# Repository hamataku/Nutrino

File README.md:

# Nutrino

**Nutrino** is a USB headphone amplifier featuring the application of the **Nutube**. It incorporates the PCM2704 as the codec IC and utilizes the NJM4580 for the operational amplifier in the output stage.

The circuit design was completed using Eagle. The schematic diagram is [here](misc/nutrino.pdf).

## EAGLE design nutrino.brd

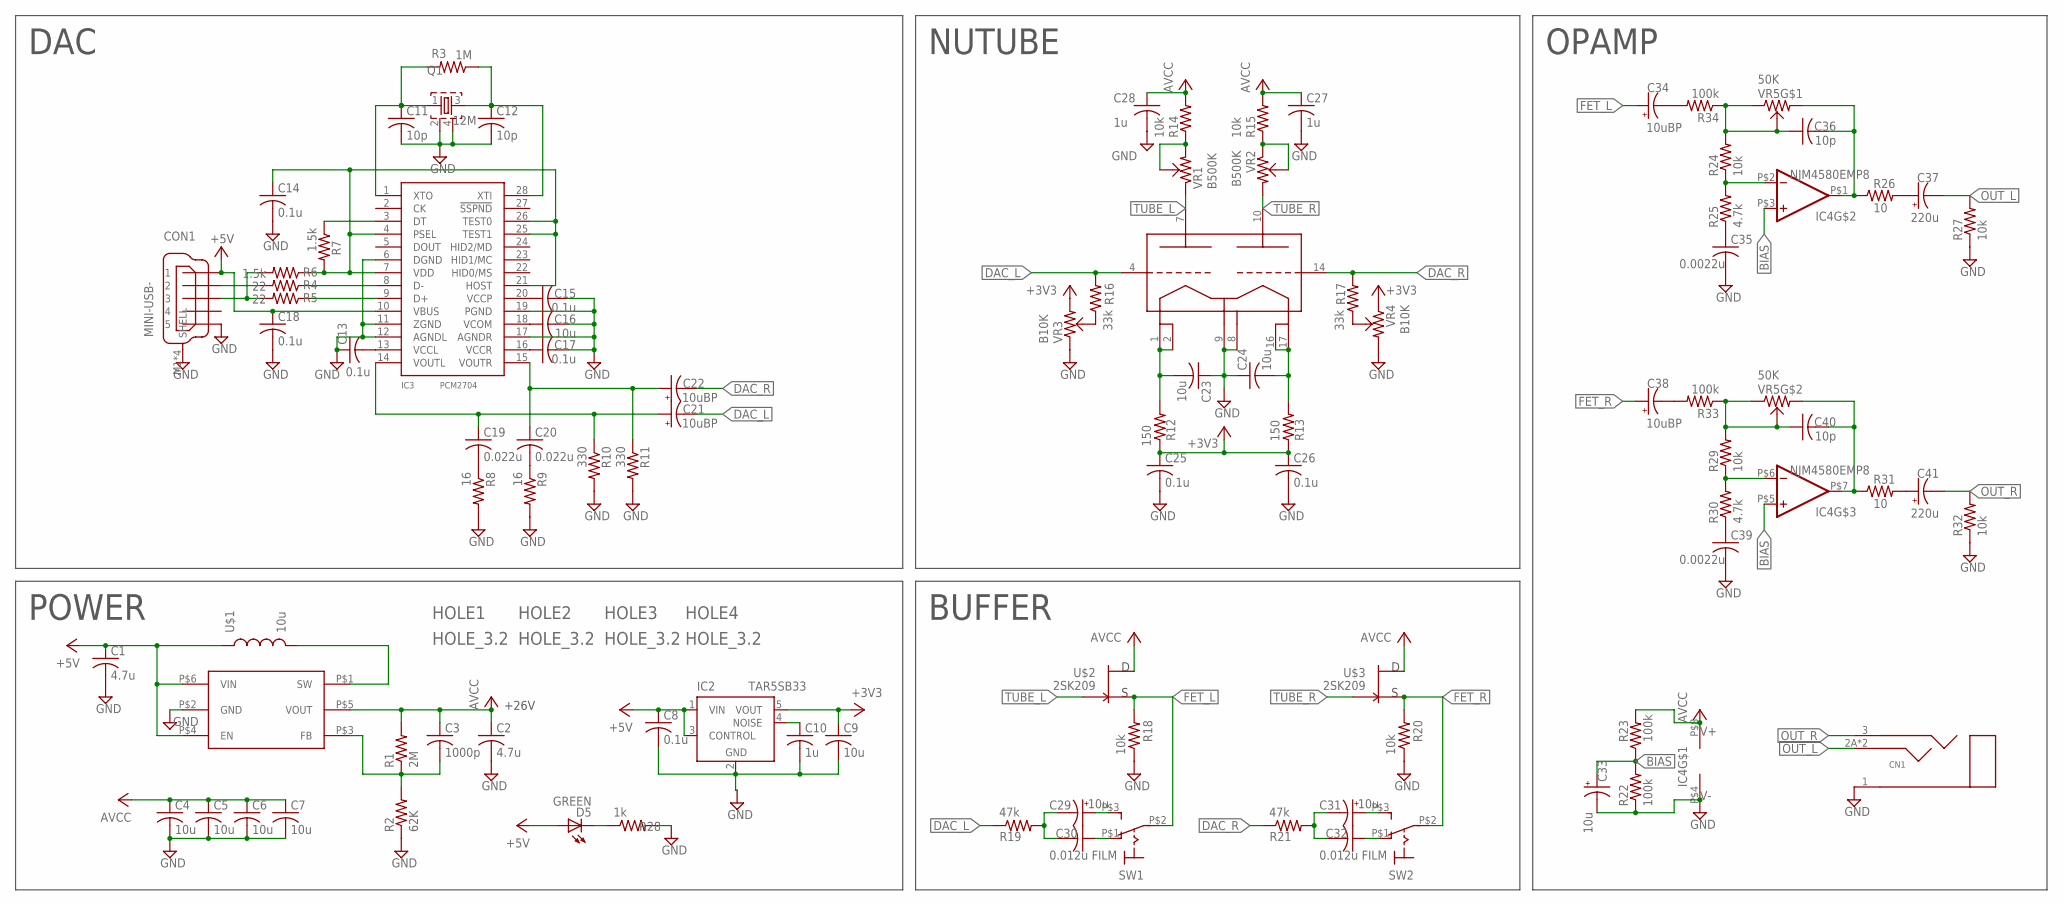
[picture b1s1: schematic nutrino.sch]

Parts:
C1, C2: 4.7u; 2012-C
C3: 1000p; 2012-C
C4, C5, C6, C7, C9: 10u; 2012-C
C8, C13, C14, C15, C17, C18, C25, C26: 0.1u; 2012-C
C10, C27, C28: 1u; 2012-C
C11, C12, C36, C40: 10p; 2012-C
C16, C23, C24: 10u; 3216
C19, C20: 0.022u; 2012-C
C21, C22, C34, C38: 10uBP; E2,5-7
C29, C31, C33: 10u; E2,5-7
C30, C32: 0.012u FILM; C050-024X044
C35, C39: 0.0022u; 2012-C
C37, C41: 220u; E2,5-7
CN1: STEREO-3.5-MJ8435; MJ8435
CON1: MINI-USB-; UX60A-MB-5ST
D5: GREEN; D2012
HOLE1, HOLE2, HOLE3, HOLE4: HOLE_3.2
IC1: TLV61046A; SOT23-6
IC2: TAR5SB33; SSOP5-P-0.95
IC3: PCM2704; SSOP28
IC4: NJM4580EMP8; EMP8
Q1: 12M; FA-238V
R1: 2M; 2012-R
R2: 62K; 2012-R
R3: 1M; 2012-R
R4, R5: 22; 2012-R
R6, R7: 1.5k; 2012-R
R8, R9: 16; 2012-R
R10, R11: 330; 2012-R
R12, R13: 150; 2012-R
R14, R15, R18, R20, R24, R27, R29, R32: 10k; 2012-R
R16, R17: 33k; 2012-R
R19, R21: 47k; 2012-R
R22, R23, R33, R34: 100k; 2012-R
R25, R30: 4.7k; 2012-R
R26, R31: 10; 4532
R28: 1k; 2012-R
SW1, SW2: SLIDESW_SS12D01G4; SS12D01G4
U1: NUTUBE_6P1_1
U$1: 10u; NR10050T
U$2, U$3: 2SK209; SC59
VR1, VR2: B500K; VR2
VR3, VR4: B10K; VR2
VR5: 50K; VR2C

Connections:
+3V3: C9.1, C25.1, C26.1, IC2.5 (VOUT), R12.1, R13.1, VR3.2, VR4.1
+5V: C1.1, C8.1, C18.1, CON1.1, D5.A, IC1.P$4 (EN), IC1.P$6 (VIN), IC2.1 (VIN), IC2.3 (CONTROL), IC3.10 (VBUS), U$1.1
AVCC: C2.1, C3.1, C4.1, C5.1, C6.1, C7.1, C27.1, C28.1, IC1.P$5 (VOUT), IC4.P$8 (V+), R1.2, R14.2, R15.2, R23.2, U$2.E (D), U$3.E (D)
BIAS: C33.+, IC4.P$3 (+IN), IC4.P$5 (+IN), R22.2, R23.1
DAC_L: C21.-, R16.2, R19.1, U1.4 (G1_4)
DAC_R: C22.-, R17.2, R21.1, U1.14 (G2_14)
FET_L: C34.+, R18.2, SW1.P$2, U$2.B (S)
FET_R: C38.+, R20.2, SW2.P$2, U$3.B (S)
GND: C1.2, C2.2, C4.2, C5.2, C6.2, C7.2, C8.2, C9.2, C10.2, C11.2, C12.2, C13.1, C14.2, C15.2, C16.2, C17.2, C18.2, C23.1, C24.1, C25.2, C26.2, C27.2, C28.2, C33.-, C35.2, C39.2, CN1.1 (SLEEVE), CON1.5, CON1.M1 (SHELL), CON1.M2 (SHELL), CON1.M3 (SHELL), CON1.M4 (SHELL), IC1.P$2 (GND), IC2.2 (GND), IC3.6 (DGND), IC3.11 (ZGND), IC3.12 (AGNDL), IC3.17 (AGNDR), IC3.19 (PGND), IC4.P$4 (V-), Q1.2, Q1.4, R2.1, R8.2, R9.2, R10.2, R11.2, R18.1, R20.1, R22.1, R27.1, R28.2, R32.1, U1.8 (GND_8), U1.9 (F2_9), VR3.1, VR4.2
unnamed: C11.1, IC3.1 (XTO), Q1.1, R3.2
unnamed: IC1.P$1 (SW), U$1.2
unnamed: C12.1, IC3.28 (XTI), Q1.3, R3.1
unnamed: C3.2, IC1.P$3 (FB), R1.1, R2.2
unnamed: IC3.9 (D+), R5.1
unnamed: IC3.8 (D-), R4.1
unnamed: CON1.2, R4.2
unnamed: CON1.3, R5.2, R6.2
unnamed: C13.2, IC3.13 (VCCL)
unnamed: C14.1, IC3.4 (PSEL), IC3.7 (VDD), IC3.21 (HOST), IC3.25 (TEST1), IC3.26 (TEST0), R6.1, R7.2
unnamed: C15.1, IC3.20 (VCCP)
unnamed: C17.1, IC3.16 (VCCR)
unnamed: C16.1, IC3.18 (VCOM)
unnamed: C19.2, R8.1
unnamed: IC3.3 (DT), R7.1
unnamed: C20.2, R9.1
unnamed: C20.1, C22.+, IC3.15 (VOUTR), R11.1
unnamed: C19.1, C21.+, IC3.14 (VOUTL), R10.1
unnamed: D5.K, R28.1
unnamed: R14.1, VR1.2, VR1.BR
unnamed: C10.1, IC2.4 (NOISE)
unnamed: C24.2, R13.2, U1.16 (F3_16), U1.17 (F3_17)
unnamed: C23.2, R12.2, U1.1 (F1_1), U1.2 (F1_2)
unnamed: C30.1, SW1.P$1 (O)
unnamed: C29.+, SW1.P$3 (S)
unnamed: R15.1, VR2.1, VR2.BR
unnamed: R16.1, VR3.BR
unnamed: R17.1, VR4.BR
unnamed: C32.1, SW2.P$1 (O)
unnamed: C31.+, SW2.P$3 (S)
unnamed: C29.-, C30.2, R19.2
unnamed: IC4.P$2 (-IN), R24.1, R25.2
unnamed: C35.1, R25.1
unnamed: C36.1, R24.2, R34.1, VR5.2 (BR), VR5.3 (1)
unnamed: C34.-, R34.2
unnamed: C36.2, IC4.P$1 (OUT), R26.1, VR5.1 (2)
unnamed: C31.-, C32.2, R21.2
unnamed: C37.+, R26.2
unnamed: IC4.P$6 (-IN), R29.1, R30.2
unnamed: C39.1, R30.1
unnamed: C40.1, R29.2, R33.1, VR5.2' (BR), VR5.3' (1)
unnamed: C38.-, R33.2
unnamed: C40.2, IC4.P$7 (OUT), R31.1, VR5.1' (2)
unnamed: C41.+, R31.2
OUT_L: C37.-, CN1.2A (RING), CN1.2B (RING), R27.2
OUT_R: C41.-, CN1.3 (TIP), R32.2
TUBE_L: U1.7 (A1_7), U$2.C (G), VR1.1
TUBE_R: U1.10 (A2_10), U$3.C (G), VR2.2

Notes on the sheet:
POWER
DAC
+26V
NUTUBE
BUFFER
OPAMP

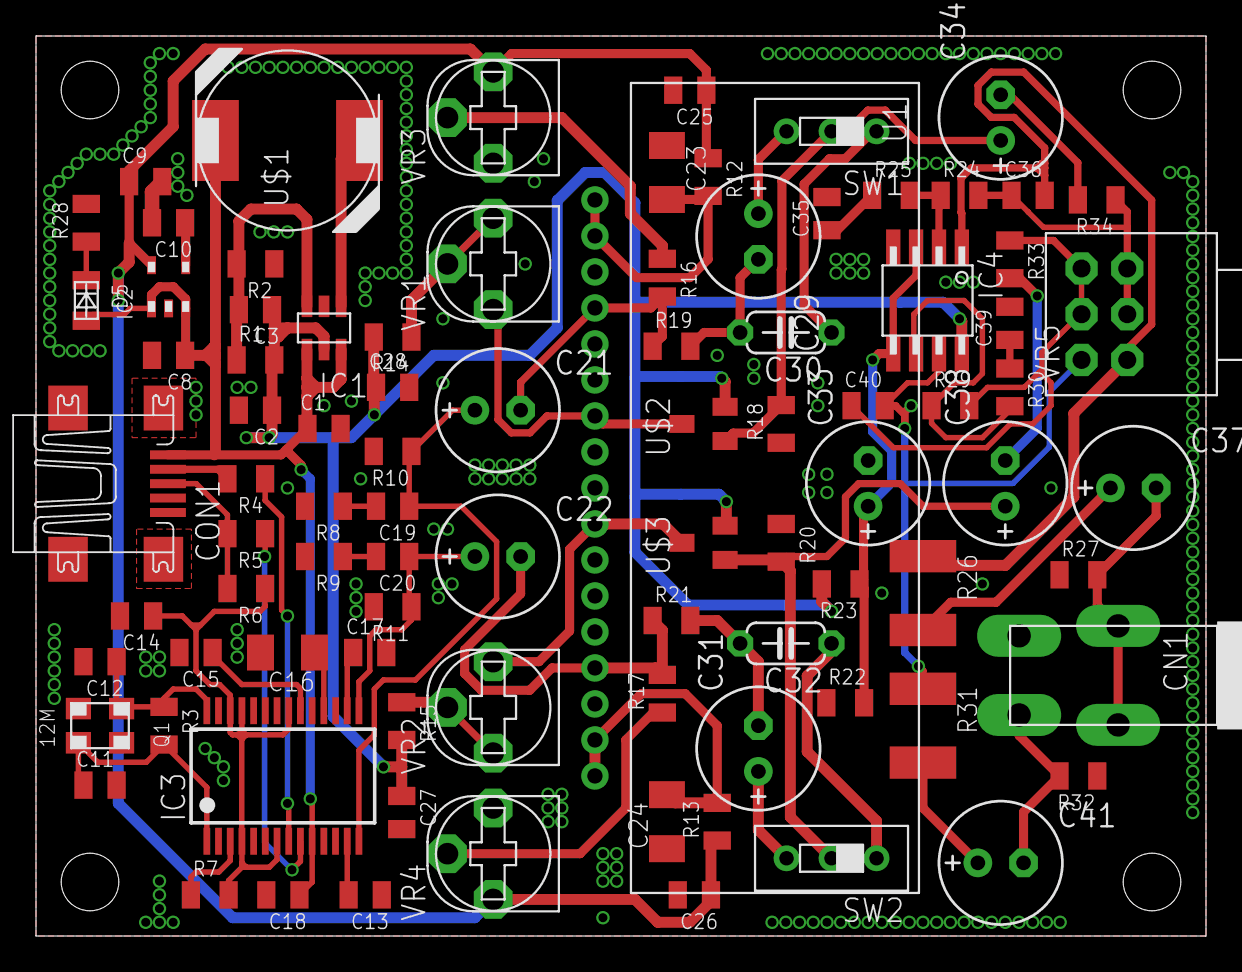
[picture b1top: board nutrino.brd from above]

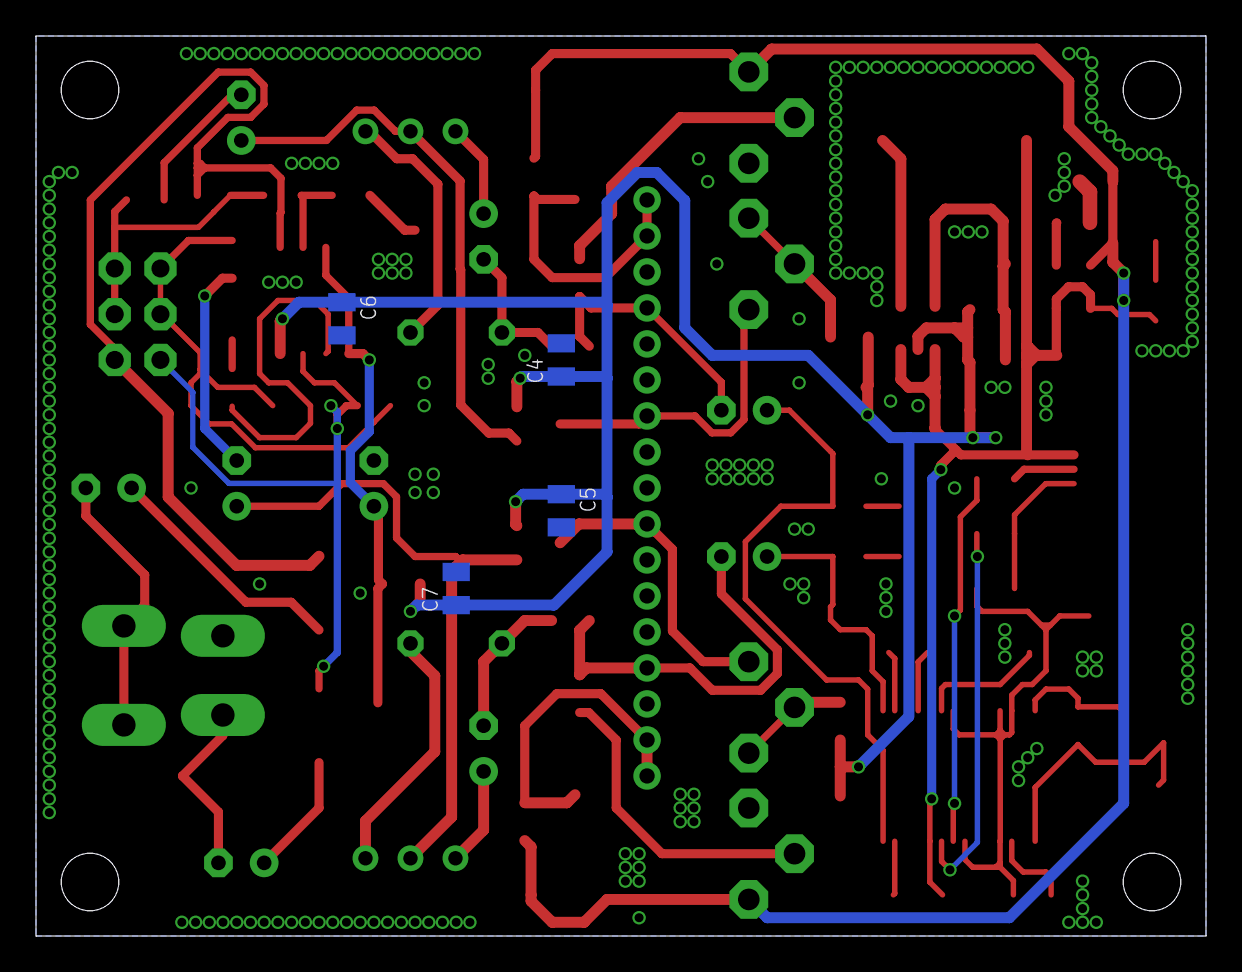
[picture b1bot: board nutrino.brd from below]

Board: 2 copper layers, 65.0 x 50.0 mm, 98 parts (4 on the bottom side), 57 nets.

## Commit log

2023-10-08 designed schematic
2023-10-09 placed parts
2023-10-09 Board diagram completed
2023-11-27 add image
2023-12-16 add schematic pdf
2023-12-16 update schematic
